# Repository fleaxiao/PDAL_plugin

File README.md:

#  PCB Design Action Labeler

PCB Design Action Labeler (PDAL) is a plugin specifically designed for KiCad that allows user to label their PCB design action to specific task number and language instructions.

PDAL and PCB Design Action Recorder ([PDAR](https://github.com/fleaxiao/PDAR_plugin.git)) are series plugins. These plugins are recommend to use together, which fully log the human's thinking during PCB design process. Please make sure the `constant.py` files in each plugin are identical.

 > **Note:** This plugin has only been tested with KiCad 8.0. It's likely incompatible with later versions.

## Setup

1. Launch `KiCad Command Prompt` and install the requirement of package in requirement.yml. 

2. Launch `KiCad` and download plugin.
    - Navigate to the folder where plugins are stored: `KiCad -> Tools -> External Plugins -> Open plugin Directory`

    - Open a terminal and change directory to the plugin folder:
        ```bash
        cd [path-to-plugins-folder]
        ```

    - Clone the PDAL_plugin repository:
        ```bash
        git clone https://github.com/fleaxiao/PDAL_plugin.git
        ```

    - Refresh your plugins in KiCad: `KiCad -> Tools -> External Plugins -> Refresh Plugins`

The PDAL plugin should now be visible in the menu of KiCad.

## Usage

1. Open both schematic file and PCB layout file. Make sure the PCB layout is empty.

2. `Initialization:` The components from the schematic will be imported to the PCB layout design environment. 

3. `Load:` The `.json` record file should be selected. 

4. `Play:` The recorded PCB design action will be played. The number of action step is controlled by the bar.

5. `Label:` After typing the specific task number and language instructions, a new label and image files will be exported.

## Acknowledge

The logo of this plugin is designed by Freepik from Flaticon.

## Contact

If you have any questions, please contact me at x.yang2@tue.nl

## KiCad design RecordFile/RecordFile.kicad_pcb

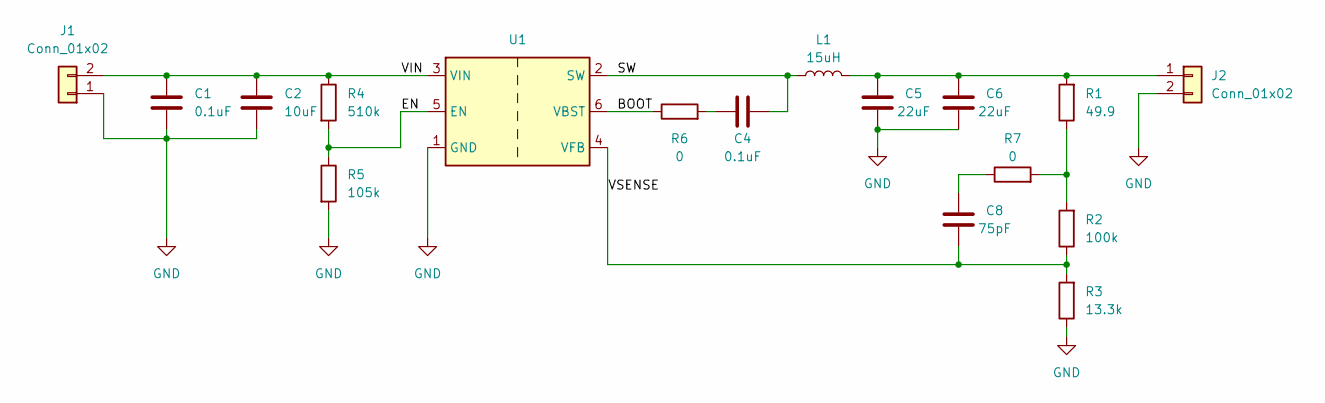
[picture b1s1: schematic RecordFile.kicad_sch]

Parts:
C1, C4: 0.1uF; C_0603_1608Metric_Pad1.08x0.95mm_HandSolder
C2: 10uF; C_1210_3225Metric_Pad1.33x2.70mm_HandSolder
C5, C6: 22uF; C_1210_3225Metric_Pad1.33x2.70mm_HandSolder
C8: 75pF; C_0603_1608Metric_Pad1.08x0.95mm_HandSolder
J1, J2: Conn_01x02; PhoenixContact_GMSTBVA_2,5_2-G_1x02_P7.50mm_Vertical
L1: 15uH; L_10.4x10.4_H4.8
R1: 49.9; R_0603_1608Metric_Pad0.98x0.95mm_HandSolder
R2: 100k; R_0603_1608Metric_Pad0.98x0.95mm_HandSolder
R3: 13.3k; R_0603_1608Metric_Pad0.98x0.95mm_HandSolder
R4: 510k; R_0603_1608Metric_Pad0.98x0.95mm_HandSolder
R5: 105k; R_0603_1608Metric_Pad0.98x0.95mm_HandSolder
R6, R7: 0; R_0603_1608Metric_Pad0.98x0.95mm_HandSolder
U1: SOT-23-6_Handsoldering

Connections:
/BOOT: R6.1, U1.6 (VBST)
/EN: R4.2, R5.1, U1.5 (EN)
/SW: C4.2, L1.1, U1.2 (SW)
/VIN: C1.1, C2.1, J1.2, R4.1, U1.3 (VIN)
/VSENSE: C8.1, R2.1, R3.2, U1.4 (VFB)
GND: C1.2, C2.2, C5.1, C6.1, J1.1, J2.2, R3.1, R5.2, U1.1 (GND)
unnamed: C4.1, R6.2
unnamed: C8.2, R7.1
unnamed: C5.2, C6.2, J2.1, L1.2, R1.2
unnamed: R1.1, R2.2, R7.2

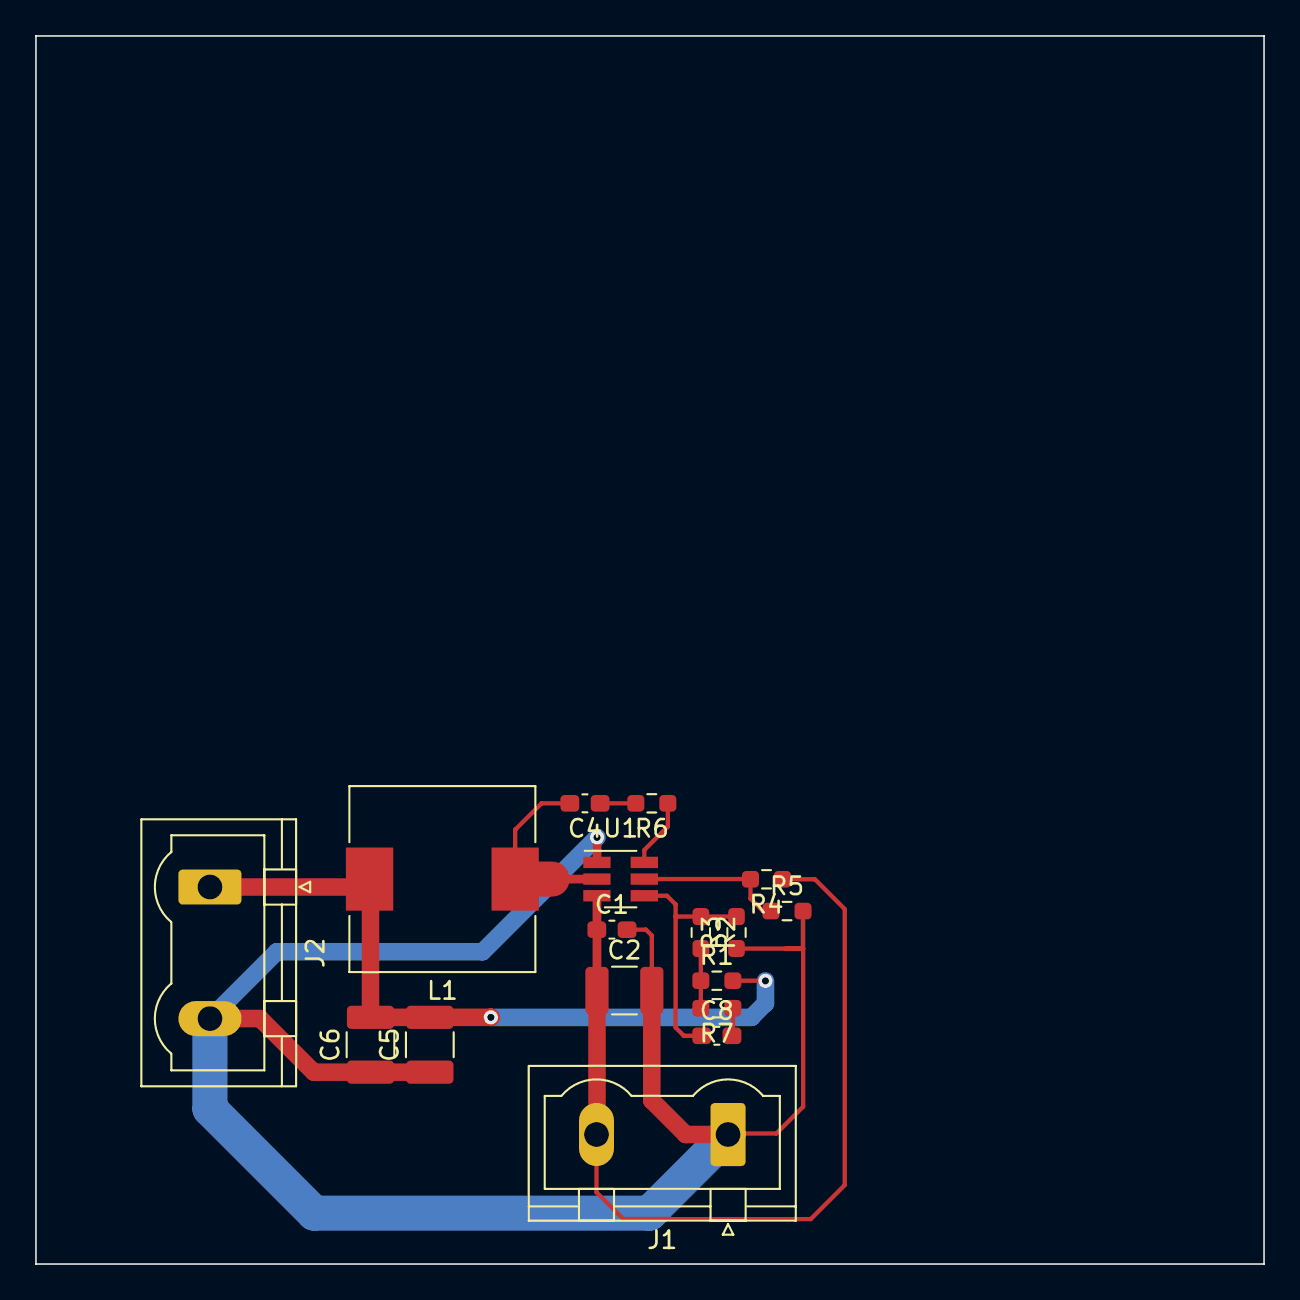
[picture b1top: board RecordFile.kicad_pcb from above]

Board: 2 copper layers, 70.0 x 70.0 mm, 17 parts (0 on the bottom side), 10 nets.

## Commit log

2024-06-14 V1.0
2024-06-16 label file and UI
2024-06-16 Instruction file
2024-06-27 highlight play
2024-07-16 requirement
2024-07-16 remove cache file
2024-07-16 remove cache file in gitignore
2024-07-19 placement version
2024-07-22 fine footprint and constraint data format
2024-11-12 remove unneccessary files
2024-11-12 remove recordfile
2024-11-13 rm test
2024-11-13 update constant
2024-11-17 V3.1
2024-11-27 v0.11
